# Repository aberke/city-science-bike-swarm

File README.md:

# [BIKE] SWARM

Project overview: https://www.media.mit.edu/projects/bike-swarm/overview/

A decentralized system of synchronized lights to coordinate urban mobility swarms.

City Science research @ MIT Media Lab

## Tech/Development Notes

#### Radio Communications

Using module nRF24L01+ 2.4Ghz

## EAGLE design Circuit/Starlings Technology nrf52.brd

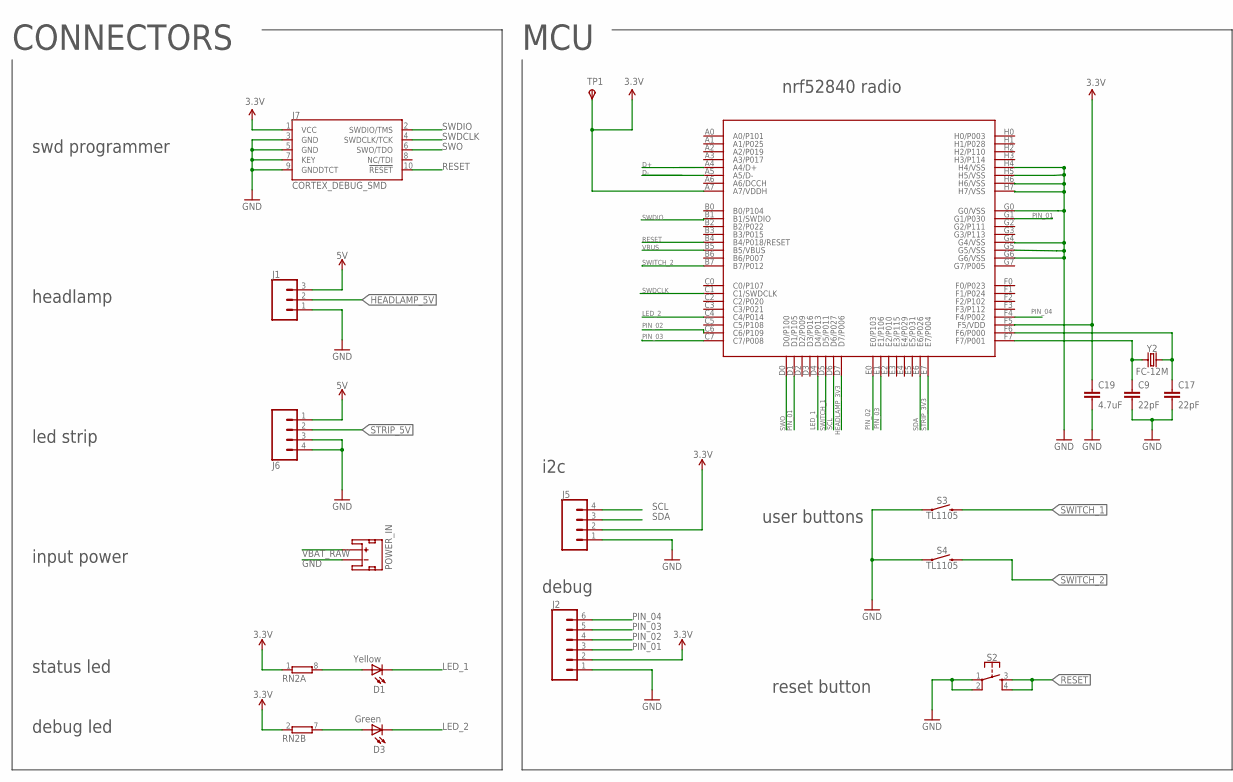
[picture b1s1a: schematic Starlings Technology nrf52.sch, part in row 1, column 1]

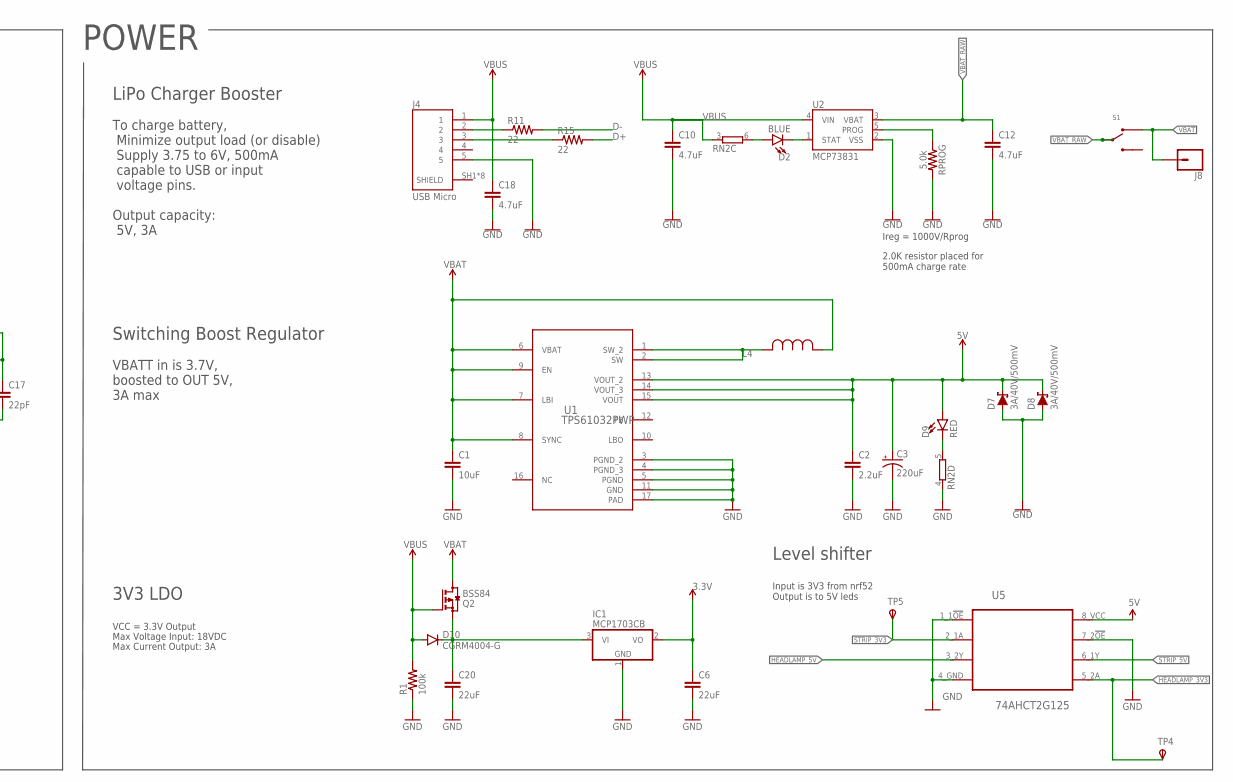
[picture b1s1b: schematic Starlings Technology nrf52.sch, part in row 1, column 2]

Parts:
C1: 10uF; 0603; DIGIKEY 587-1256-1-ND
C2: 2.2uF; 0603; DIGIKEY 1276-1040-1-ND
C3: 220uF; EIA3528; DIGIKEY 718-1106-1-ND
C6, C20: 22uF; 0805; DIGIKEY 490-10511-1-ND
C9, C17: 22pF; 0805; DIGIKEY 399-C0805C220K5HAC7800CT-ND
C10, C12, C18, C19: 4.7uF; 0603; DIGIKEY 399-3482-1-ND
D1: Yellow; LED-0603; DIGIKEY 350-4349-2-ND
D2: BLUE; LED-0603; DIGIKEY 160-1647-1-ND
D3: Green; LED-0603; DIGIKEY 754-1116-1-ND
D7, D8: 3A/40V/500mV; SMA-DIODE; DIGIKEY 3757-SBA130AS_R1_00001TR-ND
D9: RED; LED-0603; DIGIKEY 160-1436-1-ND
D10: CGRM4004-G; SOD-123_MINI-SMA; DIGIKEY 3757-SBA130AS_R1_00001TR-ND
IC1: MCP1703CB; SOT23; DIGIKEY AP2138N-3.3TRG1DICT-ND
J1: CONN_03LOCK_LONGPADS; 1X03_LOCK_LONGPADS; DIGIKEY S1111EC-03-ND
J2: CONN_06SMD-1MM; 1X06-1MM
J4: USB Micro; MOLEX_1050170001; DIGIKEY WM1399CT-ND
J5: CONN_04SMD2; 1X04_1MM_RA
J6: CONN_04LOCK_LONGPADS; 1X04_LOCK_LONGPADS; DIGIKEY S1111EC-04-ND
J7: CORTEX_DEBUG_SMD; SAMTECH_FTSH-105-01; DIGIKEY SAM1161-05-ND
J8: CONN_01; 1X01
L4: 1.0 uH; IND_BOURNS_SRR1260; DIGIKEY 308-1937-2-ND
POWER_IN: JST_2MM_MALE; JST-2-SMD; DIGIKEY 732-2711-1-ND
Q2: BSS84; SOT23; DIGIKEY DMP2215LDICT-ND
R1: 100k; 0603-RES; DIGIKEY RMCF0603FG100KCT-ND
R11: 22; 0603-RES; DIGIKEY 311-22.0HRTR-ND
R15: 22; 0603-RES; DIGIKEY 311-22.0HRCT-ND
RN2: 4R-NEXBS8V; EXBS8V; DIGIKEY YC324J-1.0KCT-ND
RPROG: 5.0k; 0603; DIGIKEY RMCF0603JT2K00CT-ND
S1: CF-LD-1DC4-AR2W; DIGIKEY 563-1946-ND
S2: MOMENTARY-SWITCH-SPST-2-SMD-4.6X2.8MM; TACTILE_SWITCH_SMD_4.6X2.8MM; DIGIKEY 401-1426-1-ND
S3, S4: TL1105; TACTILE_SWITCH_PTH_6.0MM; DIGIKEY EG2506-ND
TP1, TP4, TP5: TPSB1,27; B1,27
U1: TPS61032PWP; PWP0016K_N
U2: MCP73831; SOT23-5; DIGIKEY 497-5809-1-ND
U3: BC840M; DIGIKEY 1914-BC840MCT-ND
U5: 74AHCT2G125; VSSOP-8; DIGIKEY 1727-6544-1-ND‎
Y2: FC-12M; DIGIKEY 2195-CM8V-T1A-32.768KHZ-12.5PF-20PPM-TA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

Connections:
3.3V: C6.1, C19.1, IC1.2 (VO), J2.2, J5.2, J7.1 (VCC), RN2.1, RN2.2 (1), TP1.TP, U3.A7 (A7/VDDH), U3.F5 (F5/VDD)
5V: C2.1, C3.A (+), D7.C, D8.C, D9.A, J1.3, J6.1, U1.13 (VOUT_2), U1.14 (VOUT_3), U1.15 (VOUT), U5.8_VCC (8)
6: S1.5 (6)
D+: R15.2, U3.A4 (A4/D+)
D-: R11.2, U3.A5 (A5/D-)
GND: C1.2, C2.2, C3.C (-), C6.2, C9.2, C10.2, C12.2, C17.2, C18.2, C19.2, C20.2, D7.A, D8.A, IC1.1 (GND), J1.1, J2.1, J4.5, J5.1, J6.3, J6.4, J7.3 (GND), J7.5 (GND), J7.7 (KEY), J7.9 (GNDDTCT), POWER_IN.1 (-), R1.1, RN2.4 (1), RPROG.2, S2.1, S2.2, S3.1, S4.1, U1.3 (PGND_2), U1.4 (PGND_3), U1.5 (PGND), U1.11 (GND), U1.17 (PAD), U2.2 (VSS), U3.G0 (G0/VSS), U3.G4 (G4/VSS), U3.G5 (G5/VSS), U3.G6 (G6/VSS), U3.H4 (H4/VSS), U3.H5 (H5/VSS), U3.H6 (H6/VSS), U3.H7 (H7/VSS), U5.1_1!OE (1), U5.4_GND (4), U5.7_2!OE (7)
HEADLAMP_3V3: TP4.TP, U3.D7 (D7/P006), U5.5_2A (5)
HEADLAMP_5V: J1.2, U5.3_2Y (3)
LED_1: D1.C, U3.D4 (D4/P013)
LED_2: D3.C, U3.C4 (C4/P014)
unnamed: D1.A, RN2.8 (2)
unnamed: C9.1, U3.F7 (F7/P001), Y2.1
unnamed: L4.2, U1.1 (SW_2), U1.2 (SW)
unnamed: C20.1, D10.C, IC1.3 (VI), Q2.2 (S)
unnamed: D3.A, RN2.7 (2)
unnamed: RPROG.1, U2.5 (PROG)
unnamed: J4.2, R11.1
unnamed: D9.C, RN2.5 (2)
unnamed: D2.C, U2.1 (STAT)
unnamed: D2.A, RN2.6 (2)
unnamed: J4.3, R15.1
unnamed: C17.1, U3.F6 (F6/P000), Y2.2
PIN_01: J2.3, U3.D1 (D1/P105), U3.G1 (G1/P030)
PIN_02: J2.4, U3.C6 (C6/P109), U3.E0 (E0/P103)
PIN_03: J2.5, U3.C7 (C7/P008), U3.E1 (E1/P106)
PIN_04: J2.6, U3.F4 (F4/P002)
RESET: J7.10 (!RESET), S2.3, S2.4, U3.B4 (B4/P018/RESET)
SCL: J5.4, U3.D6 (D6/P027)
SDA: J5.3, U3.E6 (E6/P026)
STRIP_3V3: TP5.TP, U3.E7 (E7/P004), U5.2_1A (2)
STRIP_5V: J6.2, U5.6_1Y (6)
SWDCLK: J7.4 (SWDCLK/TCK), U3.C1 (C1/SWDCLK)
SWDIO: J7.2 (SWDIO/TMS), U3.B1 (B1/SWDIO)
SWITCH_1: S3.3 (2), U3.D5 (D5/P011)
SWITCH_2: S4.3 (2), U3.B7 (B7/P012)
SWO: J7.6 (SWO/TDO), U3.D0 (D0/P100)
VBAT: C1.1, J8.1, L4.1, Q2.3 (D), S1.3 (4), U1.6 (VBAT), U1.7 (LBI), U1.8 (SYNC), U1.9 (EN)
VBAT_RAW: C12.1, POWER_IN.2 (+), S1.4 (5), U2.3 (VBAT)
VBUS: C10.1, C18.1, D10.A, J4.1, Q2.1 (G), R1.2, RN2.3 (1), U2.4 (VIN), U3.B5 (B5/VBUS)

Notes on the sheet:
Max Voltage Input: 18VDC
Max Current Output: 3A
VCC = 3.3V Output
CONNECTORS
MCU
input power
led strip
Switching Boost Regulator
2.0K resistor placed for 500mA charge rate
Ireg = 1000V/Rprog
To charge battery, Minimize output load (or disable) Supply 3.75 to 6V, 500mA capable to USB or input voltage pins.
LiPo Charger Booster
Output capacity: 5V, 3A
VBATT in is 3.7V, boosted to OUT 5V, 3A max
3V3 LDO
POWER
headlamp
status led
debug led
swd programmer
nrf52840 radio
Level shifter
Input is 3V3 from nrf52 Output is to 5V leds
user buttons
reset button
i2c
debug

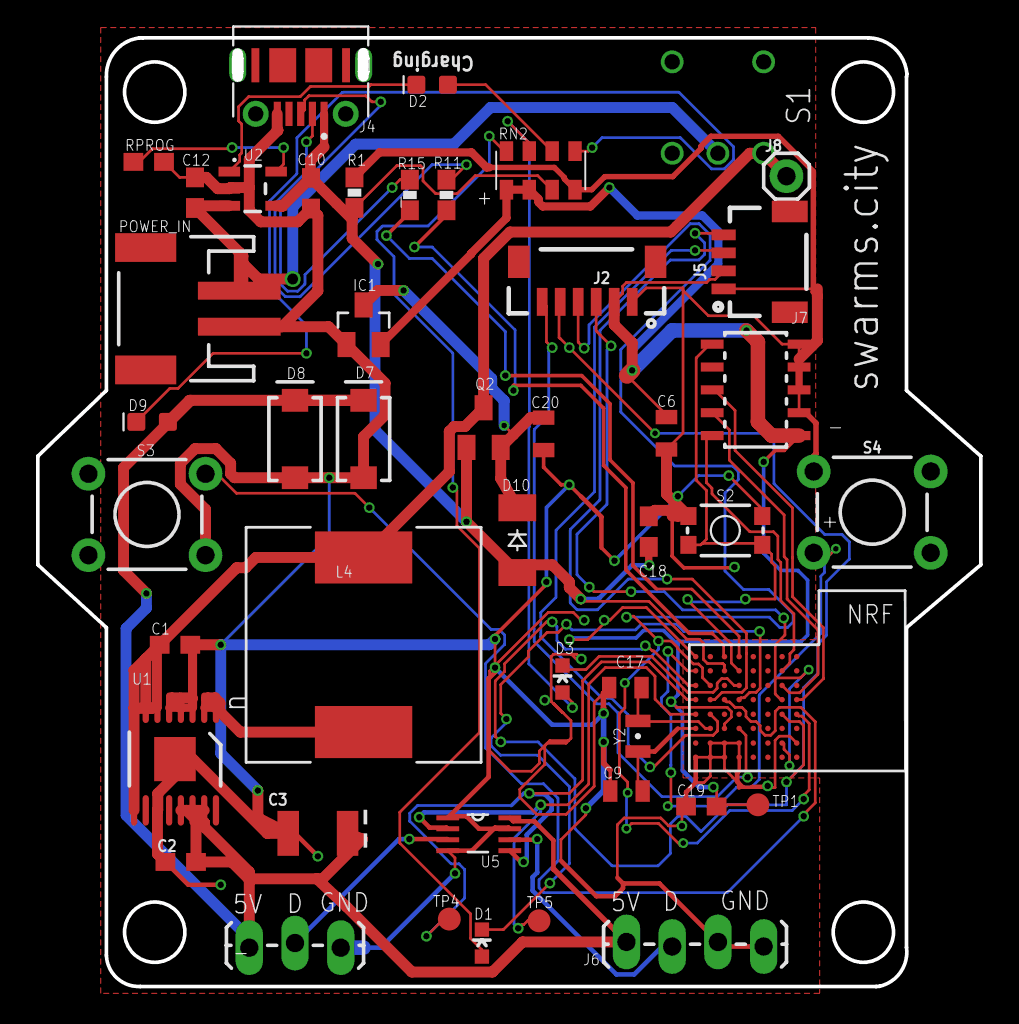
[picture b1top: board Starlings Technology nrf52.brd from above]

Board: 2 copper layers, 52.0 x 52.3 mm, 46 parts (0 on the bottom side), 38 nets.

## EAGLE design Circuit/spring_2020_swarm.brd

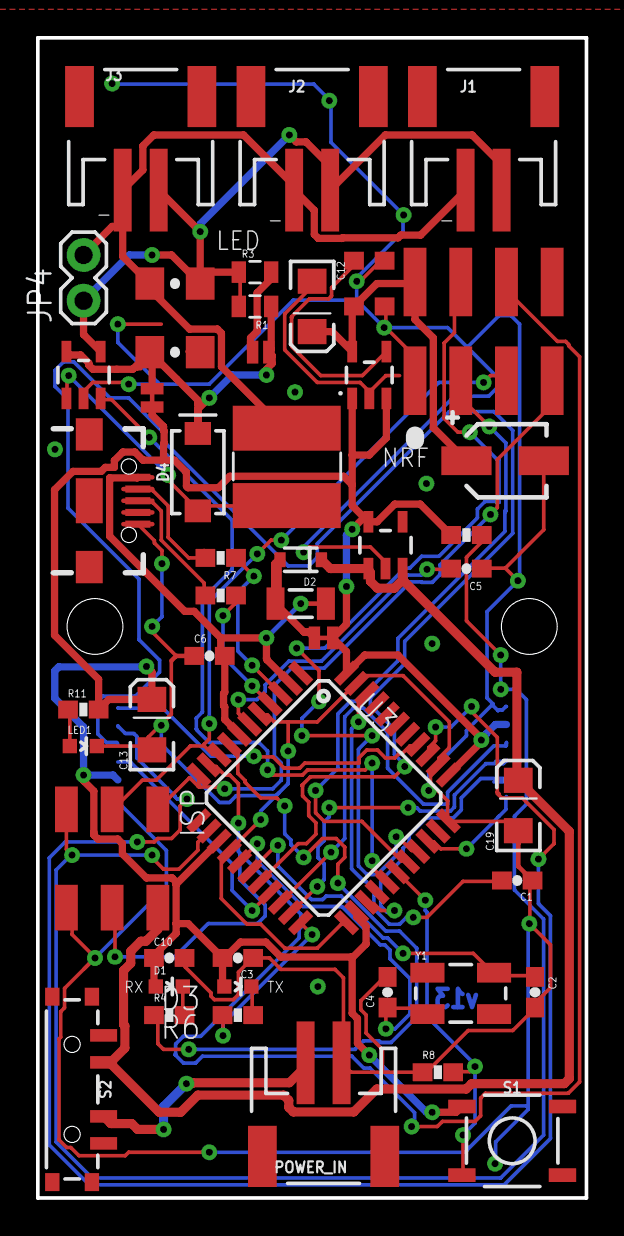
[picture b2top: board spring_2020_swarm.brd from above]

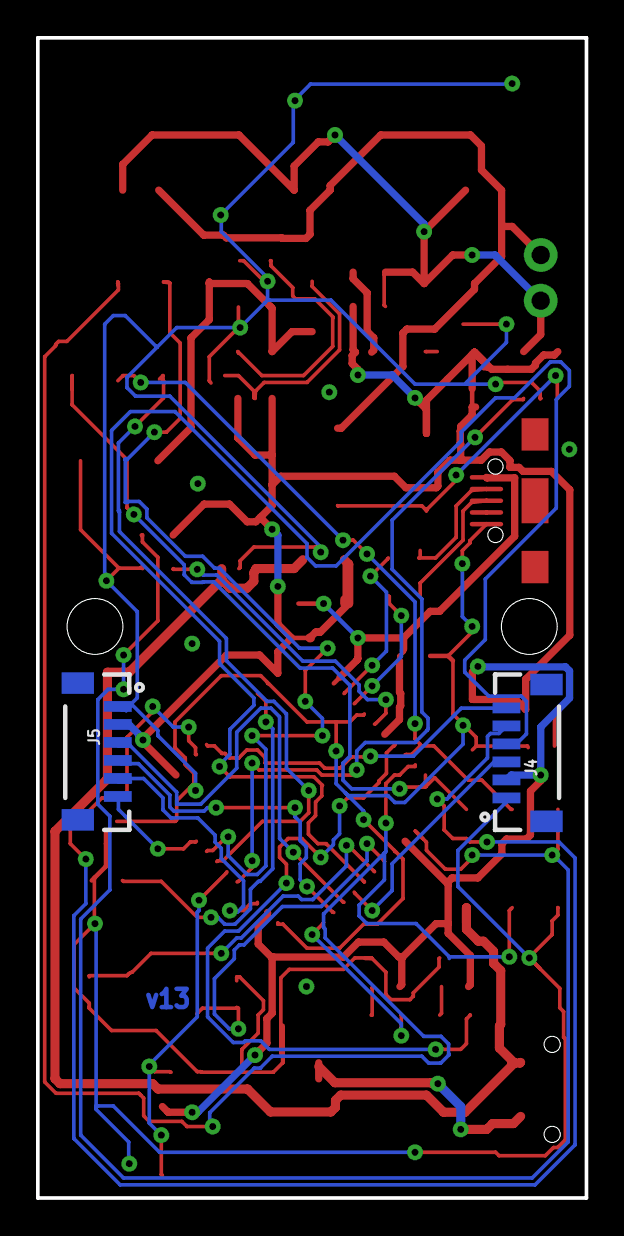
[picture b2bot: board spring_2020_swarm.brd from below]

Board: 2 copper layers, 30.5 x 64.5 mm, 51 parts (2 on the bottom side), 42 nets.

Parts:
C1, C3: 0.1uF; 0603-CAP
C2, C4: 22pF; 0603-CAP
C5, C6, C10: 1uF; 0603-CAP
C7: 1uF; 1206-CAP
C8: 2.2uF; 1206-CAP
C9: 0.1uF; 0603
C11: 4.7uF; 0603
C12, C13, C19: 10uF; EIA3216
D1: Yellow; LED-0603
D2: SOD-323
D3: Green; LED-0603
D4: 3A/40V/500mV; SMA-DIODE
F1: 500mA; PTC-1206
ISP: 2X03SMD
J1, J2, J3: JST-2-SMD
J4, J5: 1X06-1MM
JP3, JP5: JUMPER-SMT_2_NC_TRACE_NO-SILK; SMT-JUMPER_2_NC_TRACE_NO-SILK
JP4: 1X02
L1: 33uH; SRN6045
LED1: Red; LED-0603
POWER_IN: JST-2-SMD
R1, R3: 0.3R; 0805
R2: 10K; 0603-RES
R4, R6: 330; 0603-RES
R5, R7: 22; 0603-RES
R8: 10k; 0603-RES
R11: 1K; 0603-RES
S1: MOMENTARY-SWITCH-SPST-SMD-5.2MM; TACTILE_SWITCH_SMD_5.2MM
S2: SWITCH_SP3T_SMD
SJ2: NO Jumper; PAD-JUMPER-2-NO_NO_SILK
U1: AL8805; SOT23-5
U2: MIC5219; SOT23-5
U3: 32U4; TQFP44
U4: 3.3V/150mA; SOT23-5
U$4: NRFHEADSMD; 2.54MM
U$5: 33uF; PANASONIC-CAP-SMD-C
X1: USB-AB-MICRO-SMD-V03-IN&OUT
Y1: 16MHz; CRYSTAL-SMD-5X3

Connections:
3.3V: C9.1, C12.A, U4.5, U$4.2, U$5.POS
A0: J4.5, U3.36
A1: J4.6, U3.37
AREF: C1.2, U3.42
D2: J4.3, U3.19
D3: J4.4, U3.18
D4: J5.5, U3.25
D5: J5.6, U3.31
D6/CTRL_CH1: U1.3, U3.27
D8/SWITCH: R8.2, S1.3, U3.28
D9/CE: U3.29, U$4.3
D10/CSN: U3.30, U$4.4
D+: R5.1, U3.4
D-: R7.1, U3.3
GND: C1.1, C2.2, C3.1, C4.2, C5.1, C6.1, C8.2, C9.2, C10.2, C11.2, C12.C, C13.C, C19.C, ISP.6, J4.1, J5.1, LED1.C, POWER_IN.1, R8.1, U1.2, U2.2, U3.5, U3.15, U3.23, U3.33, U3.35, U3.43, U4.2, U$4.1, U$5.NEG, X1.GND1
MISO: ISP.1, U3.11, U$4.7
MOSI: ISP.4, U3.10, U$4.6
unnamed: C4.1, U3.16, Y1.1
unnamed: C2.1, U3.17, Y1.3
unnamed: D2.2, F1.2, JP5.1
unnamed: C5.2, U3.6
unnamed: D1.C, R4.2
unnamed: R7.2, X1.D-1
unnamed: D3.C, R6.2
unnamed: R5.2, X1.D+1
unnamed: R3.2, SJ2.2
unnamed: R4.1, U3.8
unnamed: C11.1, U4.4
unnamed: LED1.A, R11.1
OUT+: C7.1, J1.2, J2.2, J3.2, JP4.1, R1.2, R3.1, U1.4
OUT-: C7.2, J1.1, J2.1, J3.1, JP4.2, L1.2
RAW: C19.A, D2.1, ISP.2, S2.2, U2.1, U2.3
RAW_IN: POWER_IN.2, S2.3
RESET: ISP.5, R2.1, U3.13
RXI: J5.3, U3.20
SCK: ISP.3, U3.9, U$4.5
SW: D4.A, L1.1, U1.1
TXLED: R6.1, U3.22
TXO: J5.4, U3.21
UVCC: C6.2, F1.1, U3.2, U3.7, X1.VBUS1
VCC: C3.2, C10.1, C13.A, D1.A, D3.A, J4.2, J5.2, JP3.2, JP5.2, R2.2, R11.2, S1.1, U2.5, U3.14, U3.24, U3.34, U3.44, U4.1, U4.3
VIN: C8.1, D4.C, JP3.1, R1.1, SJ2.1, U1.5

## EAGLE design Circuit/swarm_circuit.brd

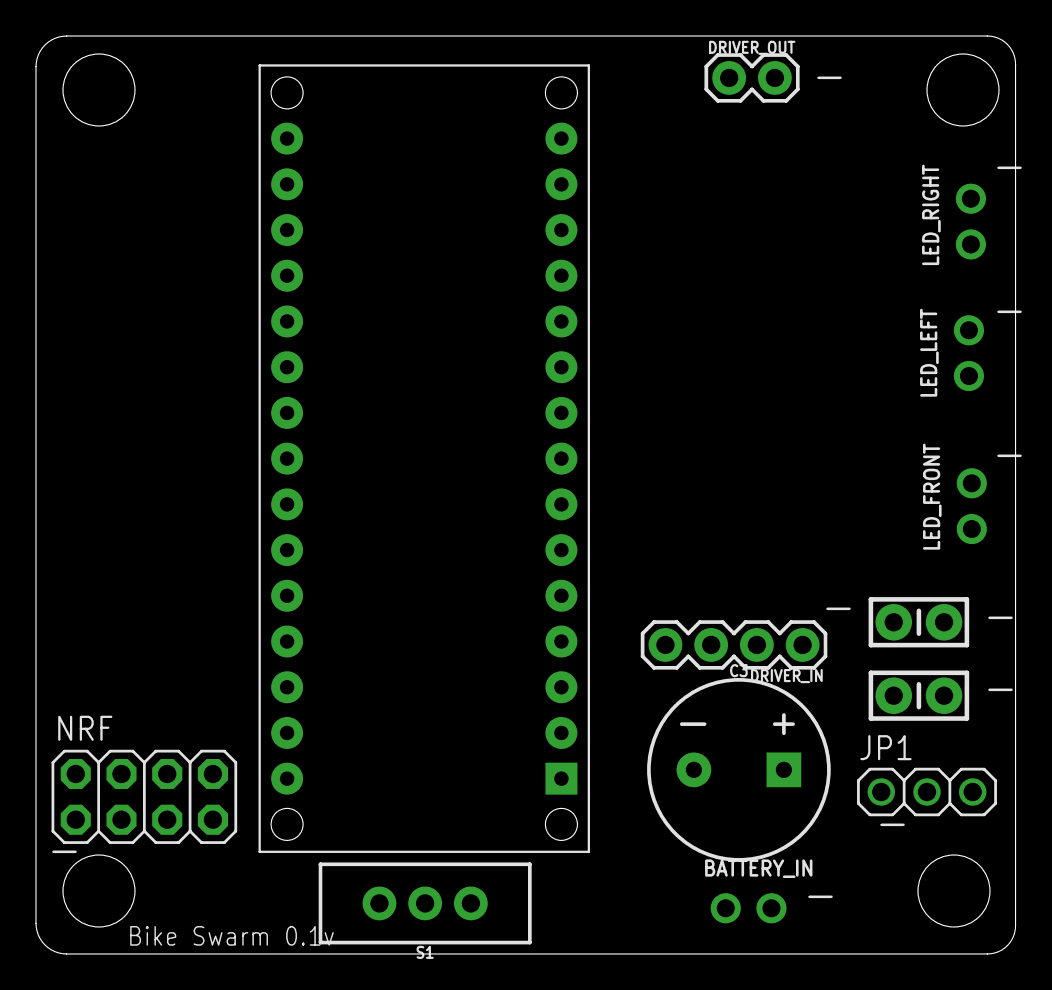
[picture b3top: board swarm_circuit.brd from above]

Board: 2 copper layers, 54.4 x 51.0 mm, 13 parts (0 on the bottom side), 14 nets, no tracks yet.

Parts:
BATTERY_IN: 1X02_ROUND
C1: 100nf; CAP-PTH-SMALL-KIT
C2: 10uf; CAP-PTH-SMALL-KIT
C3: 33uf; CPOL-RADIAL-5MM-10MM-KIT
DRIVER_IN: 1X04
DRIVER_OUT: 1X02
JP1: 1X03
LED_FRONT: 1X02_ROUND
LED_LEFT: 1X02_ROUND
LED_RIGHT: 1X02_ROUND
NRF: 2X04
S1: SWITCH_SPDT_PTH_11.6X4.0MM
U$1: ARDUINONANO; PDIP-32

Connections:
3.3V: C2.1, C3.+, JP1.2, NRF.2
5V: C1.1, JP1.3, U$1.+5V
12V: BATTERY_IN.1, S1.2
CE: NRF.3, U$1.D7
CLED: DRIVER_IN.4, U$1.D6
CSN: NRF.4, U$1.D8
GND: C1.2, C2.2, C3.-, DRIVER_IN.3, JP1.1, NRF.1, U$1.GND1
GND_IN: BATTERY_IN.2, DRIVER_IN.1
LED_GND: DRIVER_OUT.2, LED_FRONT.2, LED_LEFT.2, LED_RIGHT.2
LED_VCC: DRIVER_OUT.1, LED_FRONT.1, LED_LEFT.1, LED_RIGHT.1
MISO: NRF.7, U$1.D12
MOSI: NRF.6, U$1.D11
SCK: NRF.5, U$1.D13
VCC: DRIVER_IN.2, S1.1, S1.3, U$1.VIN

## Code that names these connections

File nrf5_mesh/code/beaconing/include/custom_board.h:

/**
 * Copyright (c) 2016 - 2020, Nordic Semiconductor ASA
 *
 * All rights reserved.
 *
 * Redistribution and use in source and binary forms, with or without modification,
 * are permitted provided that the following conditions are met:
 *
 * 1. Redistributions of source code must retain the above copyright notice, this
 *    list of conditions and the following disclaimer.
 *
 * 2. Redistributions in binary form, except as embedded into a Nordic
 *    Semiconductor ASA integrated circuit in a product or a software update for
 *    such product, must reproduce the above copyright notice, this list of
 *    conditions and the following disclaimer in the documentation and/or other
 *    materials provided with the distribution.
 *
 * 3. Neither the name of Nordic Semiconductor ASA nor the names of its
 *    contributors may be used to endorse or promote products derived from this
 *    software without specific prior written permission.
 *
 * 4. This software, with or without modification, must only be used with a
 *    Nordic Semiconductor ASA integrated circuit.
 *
 * 5. Any software provided in binary form under this license must not be reverse
 *    engineered, decompiled, modified and/or disassembled.
 *
 * THIS SOFTWARE IS PROVIDED BY NORDIC SEMICONDUCTOR ASA "AS IS" AND ANY EXPRESS
 * OR IMPLIED WARRANTIES, INCLUDING, BUT NOT LIMITED TO, THE IMPLIED WARRANTIES
 * OF MERCHANTABILITY, NONINFRINGEMENT, AND FITNESS FOR A PARTICULAR PURPOSE ARE
 * DISCLAIMED. IN NO EVENT SHALL NORDIC SEMICONDUCTOR ASA OR CONTRIBUTORS BE
 * LIABLE FOR ANY DIRECT, INDIRECT, INCIDENTAL, SPECIAL, EXEMPLARY, OR
 * CONSEQUENTIAL DAMAGES (INCLUDING, BUT NOT LIMITED TO, PROCUREMENT OF SUBSTITUTE
 * GOODS OR SERVICES; LOSS OF USE, DATA, OR PROFITS; OR BUSINESS INTERRUPTION)
 * HOWEVER CAUSED AND ON ANY THEORY OF LIABILITY, WHETHER IN CONTRACT, STRICT
 * LIABILITY, OR TORT (INCLUDING NEGLIGENCE OR OTHERWISE) ARISING IN ANY WAY OUT
 * OF THE USE OF THIS SOFTWARE, EVEN IF ADVISED OF THE POSSIBILITY OF SUCH DAMAGE.
 *
 */
#ifndef CUSTOM_BOARD_H
#define CUSTOM_BOARD_H

#ifdef __cplusplus
extern "C" {
#endif

#include "nrf_gpio.h"

// LEDs definitions for Swarm Custom Board
#define LEDS_NUMBER    4

#define LED_1          NRF_GPIO_PIN_MAP(0,13)
#define LED_2          NRF_GPIO_PIN_MAP(0,14)
#define LED_3          NRF_GPIO_PIN_MAP(0,15)
#define LED_4          NRF_GPIO_PIN_MAP(0,16)
#define LED_START      LED_1
#define LED_STOP       LED_4

#define LEDS_ACTIVE_STATE 0

#define LEDS_LIST { LED_1, LED_2, LED_3, LED_4 }

#define LEDS_INV_MASK  LEDS_MASK

#define BSP_LED_0      LED_1
#define BSP_LED_1      LED_2
#define BSP_LED_2      LED_3
#define BSP_LED_3      LED_4

#define BUTTONS_NUMBER 4

#define BUTTON_1       11
#define BUTTON_2       12
#define BUTTON_3       24
#define BUTTON_4       30
#define BUTTON_PULL    NRF_GPIO_PIN_PULLUP

#define BUTTONS_ACTIVE_STATE 0

#define BUTTONS_LIST { BUTTON_1, BUTTON_2, BUTTON_3, BUTTON_4 }

#define BSP_BUTTON_0   BUTTON_1
#define BSP_BUTTON_1   BUTTON_2
#define BSP_BUTTON_2   BUTTON_3
#define BSP_BUTTON_3   BUTTON_4

#define RX_PIN_NUMBER  8
#define TX_PIN_NUMBER  6
#define CTS_PIN_NUMBER 7
#define RTS_PIN_NUMBER 5
#define HWFC           true

#define BSP_QSPI_SCK_PIN   19
#define BSP_QSPI_CSN_PIN   17
#define BSP_QSPI_IO0_PIN   20
#define BSP_QSPI_IO1_PIN   21
#define BSP_QSPI_IO2_PIN   22
#define BSP_QSPI_IO3_PIN   23


// serialization APPLICATION board - temp. setup for running serialized MEMU tests
#define SER_APP_RX_PIN              NRF_GPIO_PIN_MAP(1,13)    // UART RX pin number.
#define SER_APP_TX_PIN              NRF_GPIO_PIN_MAP(1,14)    // UART TX pin number.
#define SER_APP_CTS_PIN             NRF_GPIO_PIN_MAP(0,2)     // UART Clear To Send pin number.
#define SER_APP_RTS_PIN             NRF_GPIO_PIN_MAP(1,15)    // UART Request To Send pin number.

#define SER_APP_SPIM0_SCK_PIN       NRF_GPIO_PIN_MAP(0,27)     // SPI clock GPIO pin number.
#define SER_APP_SPIM0_MOSI_PIN      NRF_GPIO_PIN_MAP(0,2)      // SPI Master Out Slave In GPIO pin number
#define SER_APP_SPIM0_MISO_PIN      NRF_GPIO_PIN_MAP(0,26)     // SPI Master In Slave Out GPIO pin number
#define SER_APP_SPIM0_SS_PIN        NRF_GPIO_PIN_MAP(1,13)     // SPI Slave Select GPIO pin number
#define SER_APP_SPIM0_RDY_PIN       NRF_GPIO_PIN_MAP(1,15)     // SPI READY GPIO pin number
#define SER_APP_SPIM0_REQ_PIN       NRF_GPIO_PIN_MAP(1,14)     // SPI REQUEST GPIO pin number

// serialization CONNECTIVITY board
#define SER_CON_RX_PIN              NRF_GPIO_PIN_MAP(1,14)    // UART RX pin number.
#define SER_CON_TX_PIN              NRF_GPIO_PIN_MAP(1,13)    // UART TX pin number.
#define SER_CON_CTS_PIN             NRF_GPIO_PIN_MAP(1,15)    // UART Clear To Send pin number. Not used if HWFC is set to false.
#define SER_CON_RTS_PIN             NRF_GPIO_PIN_MAP(0,2)     // UART Request To Send pin number. Not used if HWFC is set to false.


#define SER_CON_SPIS_SCK_PIN        NRF_GPIO_PIN_MAP(0,27)    // SPI SCK signal.
#define SER_CON_SPIS_MOSI_PIN       NRF_GPIO_PIN_MAP(0,2)     // SPI MOSI signal.
#define SER_CON_SPIS_MISO_PIN       NRF_GPIO_PIN_MAP(0,26)    // SPI MISO signal.
#define SER_CON_SPIS_CSN_PIN        NRF_GPIO_PIN_MAP(1,13)    // SPI CSN signal.
#define SER_CON_SPIS_RDY_PIN        NRF_GPIO_PIN_MAP(1,15)    // SPI READY GPIO pin number.
#define SER_CON_SPIS_REQ_PIN        NRF_GPIO_PIN_MAP(1,14)    // SPI REQUEST GPIO pin number.

#define SER_CONN_CHIP_RESET_PIN     NRF_GPIO_PIN_MAP(1,1)    // Pin used to reset connectivity chip

// Arduino board mappings
#define ARDUINO_SCL_PIN             27    // SCL signal pin
#define ARDUINO_SDA_PIN             26    // SDA signal pin
#define ARDUINO_AREF_PIN            2     // Aref pin

#define ARDUINO_13_PIN              NRF_GPIO_PIN_MAP(1, 15)  // Digital pin 13
#define ARDUINO_12_PIN              NRF_GPIO_PIN_MAP(1, 14)  // Digital pin 12
#define ARDUINO_11_PIN              NRF_GPIO_PIN_MAP(1, 13)  // Digital pin 11
#define ARDUINO_10_PIN              NRF_GPIO_PIN_MAP(1, 12)  // Digital pin 10
#define ARDUINO_9_PIN               NRF_GPIO_PIN_MAP(1, 11)  // Digital pin 9
#define ARDUINO_8_PIN               NRF_GPIO_PIN_MAP(1, 10)  // Digital pin 8

#define ARDUINO_7_PIN               NRF_GPIO_PIN_MAP(1, 8) // Digital pin 7
#define ARDUINO_6_PIN               NRF_GPIO_PIN_MAP(1, 7) // Digital pin 6
#define ARDUINO_5_PIN               NRF_GPIO_PIN_MAP(1, 6) // Digital pin 5
#define ARDUINO_4_PIN               NRF_GPIO_PIN_MAP(1, 5) // Digital pin 4
#define ARDUINO_3_PIN               NRF_GPIO_PIN_MAP(1, 4) // Digital pin 3
#define ARDUINO_2_PIN               NRF_GPIO_PIN_MAP(1, 3) // Digital pin 2
#define ARDUINO_1_PIN               NRF_GPIO_PIN_MAP(1, 2) // Digital pin 1
#define ARDUINO_0_PIN               NRF_GPIO_PIN_MAP(1, 1) // Digital pin 0

#define ARDUINO_A0_PIN              3     // Analog channel 0
#define ARDUINO_A1_PIN              4     // Analog channel 1
#define ARDUINO_A2_PIN              28    // Analog channel 2
#define ARDUINO_A3_PIN              29    // Analog channel 3
#define ARDUINO_A4_PIN              30    // Analog channel 4
#define ARDUINO_A5_PIN              31    // Analog channel 5


#ifdef __cplusplus
}
#endif

#endif // CUSTOM_BOARD_H

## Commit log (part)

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2019-02-25 Arduino folder
2019-02-25 pulse test
2019-02-25 first pulse
2019-02-25 finished and refactored the pulsing of the light
    Next steps:
    - receive messages from other bikes over radio
    - send messages
    - pulse in sync and test
2019-03-08 finished first pass of synchronized lighting algorithm
2019-03-13 circuit
2019-03-13 circuit update
2019-03-14 arduino
2019-03-20 added pic of aruduino uno to radio prototype wiring
2019-03-20 updated adressing to handle N nodes, with addresses determined by modular arithmetic
    - also updated allowed phase shift to choose min(allowedPhaseShift,loop time)
2019-03-20 verified that it works with N nodes.
    - fixed NodeNumber from bool to int
    - added testLight for analog
2019-04-01 made changes, most notably that nodes change phase to match HIGHER phase
    also:
    - renamed radioTransmit to radioBroadcast
    - nodes receive before they send
    - allowedPhaseShift better computed
    - nodes send more frequently
    - read all messages from queue
2019-04-06 inverted defaultPhase = 0
2019-04-06 updated pins for nano
2019-04-10 pin change and light amplitude function change
    - light amplitude is determined by sinusoidal curve instead of linear path
    - changed LED pin for prototype with arduino nano from 3 to 6
2019-04-10 tuned radio frequency: range ~ 5 meters
2019-04-10 removed unused NANO boolean
2019-04-15 Fixed documentation typo
2019-04-18 updated circuit board -- aesthetic changes only
2019-04-18 removed unneeded circuit board files
2019-04-25 added bikes pulsating gif
2019-04-25 added link to project overview + GIF to README
2019-05-02 bikes
2019-05-13 fixed arduino code
2020-05-08 Icons Folder!
    png files of icons and master illustrator file
2020-05-08 icons!
    Wesbite icon png files with the master illustrator file
2020-07-12 Site Icons and Logo
2020-07-27 Adding in nrf52 and nrf52 mesh examples. The broadcast example is not yet working but having received an nrf52-DK yesterday, I finally have the ability to debug.
2020-08-04 Trying out segger embedded
2020-08-06 Stubbing in v3 of the board
    - nrf52 module BC840M from Fanstel (US firm)
    - https://www.fanstel.com/bc840m-compact-nrf52840-module
2020-08-06 Adding VScode configs.
2020-08-26 nrf52832 -> nrf52840
2020-08-27 Adding pwm fade to LEDs. Still needs timer reset and beacon hookup.
2020-08-31 Stubbing in GPIO outputs for lights.
2020-08-31 VSCode settings.
2020-08-31 Fixing Makefile.
2020-08-31 LEDs now PWM correctly with new pinout. Now to hook up to a button for blink resynchronization.
2020-09-04 Stubbing in button control to reset LED sync.
2020-09-04 Button controls
2020-09-09 Moving around nrf5 code to accomodate switch to mesh.
2020-09-18 Adding RGB for high current LED.
2020-09-18 Board components chosen and placed. Needs routing and enclosure correction. Includes 3 channel high current LED and LED strip.
2020-09-18 Adding WIP BOM.
2020-09-22 Adding MIC5205 for 3V3 LDO and using a 5V LDO. Also adding a level shifter so the nrf52 can talk to the 5V led strip. Ready to route!
2020-09-22 Removing unused connectors. Needs charging circuit.
2020-09-24 Switching from linear 5V regulator to switching 5V regulator due to 3A of current instead of 500mA.
2020-09-28 Adding in charge circuit and switching from regulator to booster 5V 2A.
2020-09-30 Finishing up v3 board. Ready to send to the board house!
2020-10-13 Fusion 360 sync.
2020-10-16 Switch to Molex USB Micro connector.
2020-10-16 Stubbing in nrf5 gcc Makefile-based mesh.
2020-10-19 Moving nrf52 module onto board.
2020-10-21 Moving around labels for better legibility.
2020-11-04 Replacing 3V3 -> 5V booster footprint, relaying out with datasheet recommendations. Still need to swap screw terminals for JST connectors on high current LEDs, find a better micro USB connector (with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
2020-11-06 Switching USB micro footprint to match the digikey component. Also switching out JSTs for 2-pin screw terminals on high current LEDs. We'll see how reliable those are, may need to switch to a latchin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
2020-11-19 Adding Digikey part numbers to all 40 components. Total BOM: .04. Also switching 5V boost controller IC due to availability.
2020-11-20 Adding a 32.768k crystal (and 22pF bypass caps for a 12.5pF capacitive load). Need to move the battery around and make room for the button.
2020-11-21 Submitting fourth board iteration. Moved components around to work better in enclosure. New USB connector, new 5V booster, added four test points, and moved pins around to match BSP on board (buttons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
2020-11-23 Updating Gerbers.
2020-12-04 Updating digikey part numbers to better match board.
2020-12-05 Using SES for nrf5 mesh code. Use the nrf5_mesh/code/beaconings/s140 SES project.
2020-12-07 circuit change, USB pins, VCC, P-MOS, vdiv
2020-12-07 Trying to track down issues, cleaning up ERC.
2020-12-08 updated traces
2020-12-08 traces gnd, and clean up
2020-12-10 fix ERC msgs
2020-12-10 Adding digikey part number for 3v3 LDO (MIC5205 - 576-1259-1-ND)
2020-12-10 osh pack drc check
2020-12-16 22pF != 22uF
2020-12-22 Fixing a few mistaken digikey part numbers.
2021-01-07 Adding neopixel I2S handling.
2021-01-07 Pulsating the led strip.
2021-01-19 switch update
2021-01-19 clean brd
2021-01-19 Updating API, attempting to fix sync issue.
2021-01-20 Rev 6 of the board is laid out and done, except for VDIV. Need to confirm what it's for and then send to the board house.
2021-01-20 Adjusting placement of silkscreen indicators.
2021-01-21 clean brd issues
2021-01-21 Adding digikey parts, updating bom for rev6.
2021-01-21 clean traces
2021-01-21 traces
2021-02-02 Updating digikey parts.
2021-02-04 Changing pins to match board.
2021-02-16 Switch to new phase when detected. Majority does not rule, which needs to be fixed.
2021-03-11 Removing picobuck, touching up and finalizing schematic layout, switching to neopixel 3W led (headlamp). Needs new dimensions to fit with battery in enclosure.
2021-03-13 Finishing V7 of the board. All connectors are on two sides of the board now, making the enclosure more seamless. Off to the board house!
2021-03-13 Updating with in stock digikey components. Subbing adjustable boost converter for fixed.
2021-03-24 Archiving old code to simplify repo.
2021-03-24 Layout of component name and adding the value of the 10k.
2021-03-24 Formatting and applying a timer since boot for phase battles
2021-04-12 board update
2021-04-15 Updating BOM for v7
2021-04-16 Adding WS2811 (headlamp) datasheet which took emailing ipixel to finally get.
2021-04-26 Adding nrf52-vs-swarm distinction on the status leds.
2021-04-27 Switching to headlamp. Need to hook up button to switch between headlamp and led strip.
2021-05-03 Removing build dir
2021-05-05 Adjusting silkscreen names.
2021-05-05 Logging timealive to see if there's a reason why the new node sends non-zeroed data.
2021-05-10 Moving from millis timealive to seconds timealive.
2021-05-14 updated footprints level-shifter, cystral and connetors
2021-05-18 Stubbing in GATT light service for Bluetooth. Doesn't work yet.
2021-05-21 Code now compiles, linking fails.
2021-05-24 V8 of the board, ready to print.
2021-05-27 Everything compiles and links. Now to debug the bluetooth gatt.
2021-05-28 Boot breaks at flash manager. Something about GATT has caused mesh to lose its placement or something, and it's failing when reading the flash storage.
2021-06-10 update board
2021-06-16 Adding state machine diagram (use draw.io to view).
2021-06-23 Adding BSP for button handling. Only works on nrf52-DK, needs proper pin assignment for swarm custom board. Also adding neopixel SPI control, although it doesn't pulse anymore due to hanging. WIP.
2021-06-23 Adding BC840M datasheet for nrf52 radio module.
2021-06-23 Adding nrf5 examples code, even though they're huge.
2021-06-24 fix traces gnd
2021-06-24 Moving to nrf52840-DK BSP pins for buttons and leds. Also driving LEDs with active LOW.
2021-06-24 Adding debugging pins for switch and leds.
2021-06-24 Revision 9 routed and ready to go to the printer.
2021-06-25 Updating revision number on back of board.
2021-07-07 Updating gerbers, adding documentation for firmware.
2021-07-07 Adjusting pins for rev 9 board, increasing interrupt priorities for SPI, adjusting timings for SPI. Both headlamp and tube light now work. Need to hook up button to change colors.
2021-07-07 DNC on a few components.
2021-07-09 new components
2021-07-09 Updating BOM
2021-07-10 Fixing issue with timealive not being read correctly. Turns out when I reduced the timer to use seconds instead of ms, I reduced the size of the timealive from 4 bytes to 2 bytes, so didn't change th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
2021-07-12 Cycling colors on button press. Now to send over the air.
2021-07-12 Changing colors based on mesh signal. Needs timealive handler to jump in order to beat seniority.
2021-07-12 Abstracting out swarm state to hold on to timealive, letting multiple modules modify it. Colors now transmit between nodes, although only when the phase is 0.
2021-07-14 Shifting phase by PI to force light syncing and change to happen at the dimmest value, not brightest.
2021-07-14 Limiting pulse anytime more than a single led channel is lit due to battery discharge capacity.
2021-07-29 Fix for phase reset issue. Turns out the hardware timer we were using for counting time was being written to by some SoftDevice bluetooth mesh code, messing up the timer for a couple seconds. Switchi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
2022-02-22 Moving v3 nrf52 board to archive, renaming to new Starlings Technology nrf52. Now to begin working on the next revision: battery swap, 1 player mode, and a smaller enclosure that's easier to mount to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
2022-03-02 Adding new rocker switch and two tactile switches. Footprints are drawn and ready, just needs routing.
2022-03-03 Adjusting dimensions, adding pins to expansion header, connecting second switch.
2022-03-11 Revision 10
    - Adding second tactile switch
    - Adjusting board dimensions to place buttons
    - Adding rocker on/off switch
2022-03-14 Adjusting traces, submitting to board house.
2022-03-15 Wire stubs are OK
2022-03-16 Switching 3.5mm terminal blocks to 2.54mm (0.1") pitch header pins for painless led attachment. Also making buttons perfectly symmetric.
2022-03-29 Adding second button, instant color transfer.
2022-04-05 Cleaning up neopixel code.
2022-04-05 Updating color every 200ms (instead of every 2ms in one extreme and every 2.5s in the other extreme).
2022-04-05 Synchronizing phase when changing clock. So now lights can be changed to a new pattern and the rest of the group follow within 200ms.
2022-04-05 Adding animation easing library.
2022-04-05 Adding alias to segger project since I have to restart the program every third time I flash.
2022-04-05 Forgot to offset colors when adding the 2 byte phase.
2022-04-05 Stubbing in patterns on top of colors. Need to refactor colors away from color patterns and towards another namespace.
2022-04-13 Revision 11 of the board, with in stock and bigger boost converter and inductor.
2022-04-14 Moving from 24 bit color to 8 bit color to winnow down the broadcast message from 14 bytes to 12 bytes.
2022-04-14 Compressing phase from 2 bytes to 1 byte. Down to 11 bytes advertising.
2022-04-14 Turning sync on/off depending on time since last broadcast received.
2022-04-14 The inSync flag needs to be checked after updating the timealive counter.
2022-04-15 Stubbing in state sync state machine. Will be used for transition animations.
2022-04-15 Undo vscode change
2022-04-15 Cleaning up before new pattern. Moved color to color.c to include new hue shifting algorithm.
2022-04-15 Stubbing in more patterns. Now able to switch between patterns.
2022-04-26 Switching to new tactile switches, separating external interfaces for easier reach and to get around enclosure ties.
2022-04-28 Revision 12, changes out buttons and resistors.
    - PTH tactile switches for taller buttons
    - Resistor array and digikey swap
2022-05-18 Bigger resistor array
2022-05-18 Attempting to remove state of meteor movement, but need to fix misalignment when meteor has already passed.
2022-05-23 Fixing bug where meteor progress > 1 would reset the lights to full brightness.
2022-05-23 New fire pattern.

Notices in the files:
parts and their libraries:
SparkFun-Connectors: Licensing: Creative Commons ShareAlike 4.0 International - https://creativecommons.org/licenses/by-sa/4.0
SparkFun-Capacitors: Licensing: CC v3.0 Share-Alike You are welcome to use this library for commercial purposes.
